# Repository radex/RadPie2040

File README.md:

# RadPie2040

A RP2040-based board, similar to [Raspberry Pi Pico H](https://www.raspberrypi.com/products/raspberry-pi-pico/), featuring:

- RP2040 microcontroller
- 16MB Flash
- breadboard-friendly pin headers with labels (+ debug header)
- USB-C connector
- BOOTSEL *and* RESET buttons
- **JLCPCB Assembly optimized**, 2-layer board
- KiCad 8 template, hierarchical schematic

**DISCLAIMER**: This board was designed as an exercise. It has not (yet) been manufactured and tested. Also, **I don't know what I'm doing**, this is like the third PCB I've designed. Don't use it lol.

|  |  |  |
| -- | -- | -- |

## Credits and learning resources

This project is a fork of [Sleepdealr/RP2040-designguide](https://github.com/Sleepdealr/RP2040-designguide). It bears little resemblance to the original, but it was a great starting point (and still contains some pieces of it).

I also took a lot of inspiration and knowledge from these YouTube videos:

- [MicroType Engineering - RP2040 KiCad 6 Hardware Design](https://www.youtube.com/watch?v=RNH-CL8GrF8)
- [Phil’s Lab - Raspberry Pi RP2040 Hardware Design](https://www.youtube.com/watch?v=X00Cm5LMNQk)

There's extra learning resources in the `Resources/` folder (copied from Sleepdealr's project).

## Components

This board is optimized to use JLCPCB Basic (or Extended Preferred) components as much as possible to make it cheap to manufacture at 2-5 pieces scale.

Some worth mentioning:

- Flash: C97521 - Winbond W25Q128JVSIQ - 128Mbit (16MB) NOR Flash
- Voltage Regulator: C5446 - XC6206
- Crystal: C9002 - 12MHz
- Buttons: C318884 - TS-1187A-B-A-B
- TVS diodes: C7420376 - SRV05-4

Most components are the same as in [Sleepdealr's design](https://github.com/Sleepdealr/RP2040-designguide). Differences: larger Flash, different TVS diodes, added buttons, power LED indicator, removed resettable fuse.

**Extended parts**: The only parts that are not on JLCPCB's Basic parts list (i.e. you'll pay $3 feeder fee per part) are the RP2040 and the USB-C connector. (Pin headers are not on the BOM, but you can add them).

## Customizability

Some things to consider:

- The 0Ω 1206 resistor is a placeholder for a resettable fuse. (There are none in JLC's Basic parts, but it's a good idea to have one)
- Flash storage and buttons could be replaced with smaller physical packages
- For size/cost/simplicity, you can remove buttons, USB, TVS, fuse placeholder, LED if you don't need them. You could even remove the crystal and rely on RP2040's ring oscillator if you don't need precise timing or max performance

## TODO

- Have this board manufactured, see if it works!
- I'm concerned about the crystal, it seems to me that layout and loading capacitors could be better, but they can be finnicky, and Sleepdealr's design works, so I didn't change anything.
- I'm thinking of designing a smaller version, optimized for use as a module with carrier boards (using 1mm pitch pin headers, not castellated holes like the original Pico for cost reasons)

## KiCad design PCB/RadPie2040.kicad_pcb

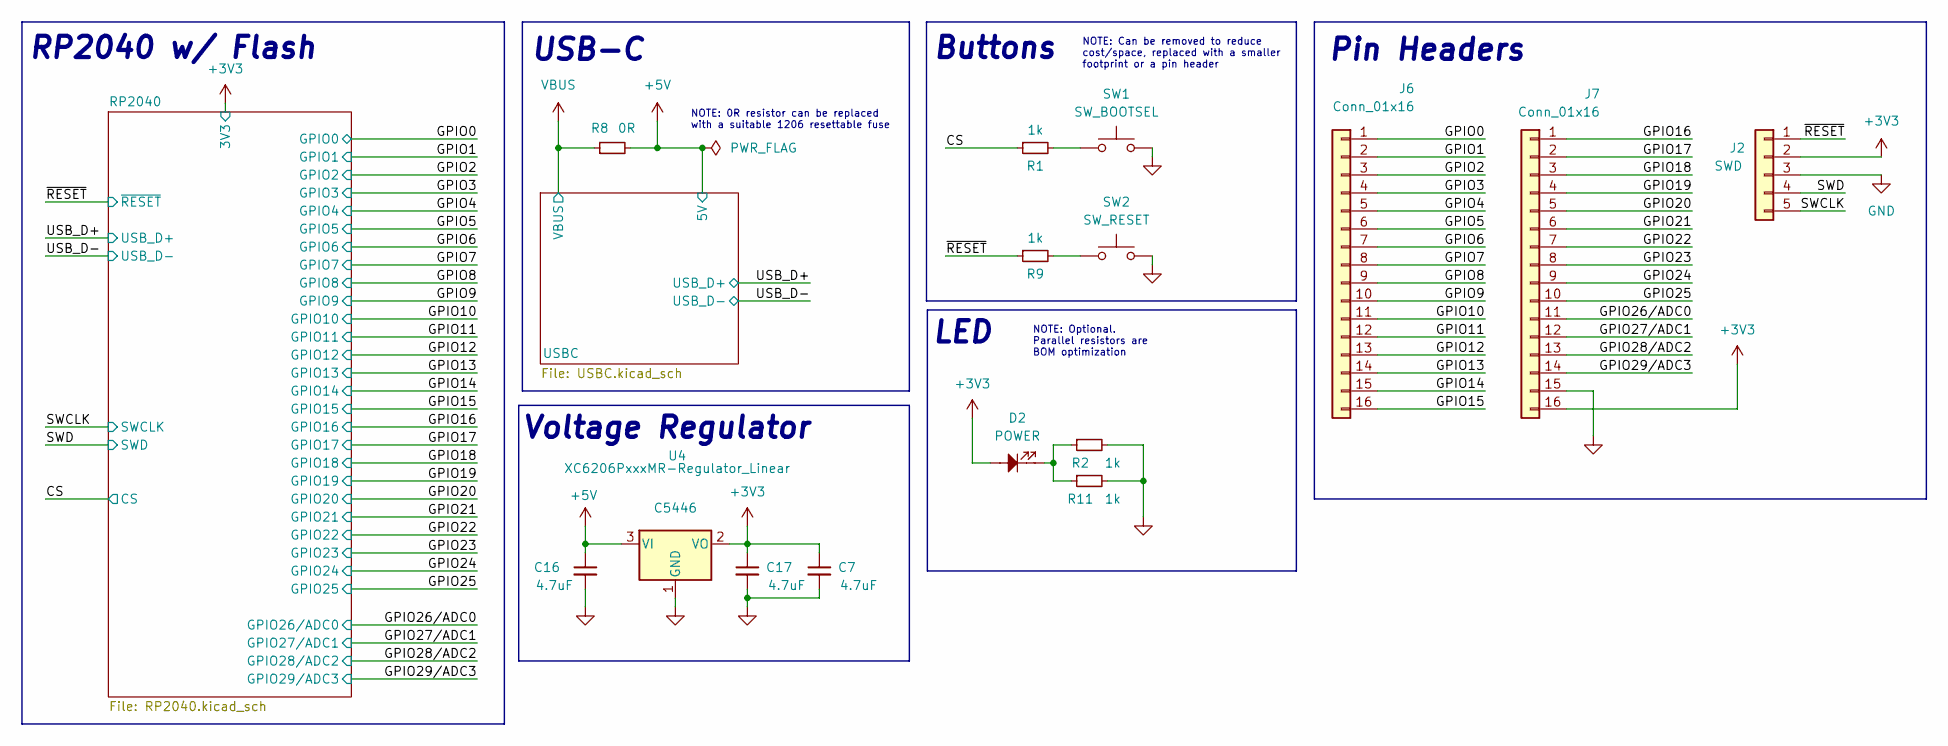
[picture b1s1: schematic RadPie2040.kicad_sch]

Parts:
C7, C16, C17: 4.7uF; C_0805_2012Metric; LCSC C1779
D2: POWER; LED_0603_1608Metric_Dot; LCSC C2286
J2: SWD; PinSocket_1x05_P2.54mm_Vertical
J6, J7: Conn_01x16; PinHeader_1x16_P2.54mm_Vertical
R1, R2, R9, R11: 1k; R_0402_1005Metric; LCSC C11702
R8: 0R; R_1206_3216Metric; LCSC C17888
SW1: SW_BOOTSEL; TS-1187A-B-A-B; LCSC C318884
SW2: SW_RESET; TS-1187A-B-A-B; LCSC C318884
U4: XC6206PxxxMR-Regulator_Linear; SOT-23; LCSC C5446

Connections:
+3V3: C7.1, C17.1, D2.2, J2.2, J7.16, U4.2 (VO); also elsewhere on the board
+5V: C16.1, R8.2, U4.3 (VI); also elsewhere on the board
/CS: R1.1; also elsewhere on the board
/GPIO0: J6.1; also elsewhere on the board
/GPIO1: J6.2; also elsewhere on the board
/GPIO2: J6.3; also elsewhere on the board
/GPIO3: J6.4; also elsewhere on the board
/GPIO4: J6.5; also elsewhere on the board
/GPIO5: J6.6; also elsewhere on the board
/GPIO6: J6.7; also elsewhere on the board
/GPIO7: J6.8; also elsewhere on the board
/GPIO8: J6.9; also elsewhere on the board
/GPIO9: J6.10; also elsewhere on the board
/GPIO10: J6.11; also elsewhere on the board
/GPIO11: J6.12; also elsewhere on the board
/GPIO12: J6.13; also elsewhere on the board
/GPIO13: J6.14; also elsewhere on the board
/GPIO14: J6.15; also elsewhere on the board
/GPIO15: J6.16; also elsewhere on the board
/GPIO16: J7.1; also elsewhere on the board
/GPIO17: J7.2; also elsewhere on the board
/GPIO18: J7.3; also elsewhere on the board
/GPIO19: J7.4; also elsewhere on the board
/GPIO20: J7.5; also elsewhere on the board
/GPIO21: J7.6; also elsewhere on the board
/GPIO22: J7.7; also elsewhere on the board
/GPIO23: J7.8; also elsewhere on the board
/GPIO24: J7.9; also elsewhere on the board
/GPIO25: J7.10; also elsewhere on the board
/GPIO26/ADC0: J7.11; also elsewhere on the board
/GPIO27/ADC1: J7.12; also elsewhere on the board
/GPIO28/ADC2: J7.13; also elsewhere on the board
/GPIO29/ADC3: J7.14; also elsewhere on the board
/SWCLK: J2.5; also elsewhere on the board
/SWD: J2.4; also elsewhere on the board
/~RESET: J2.1, R9.1; also elsewhere on the board
GND: C7.2, C16.2, C17.2, J2.3, J7.15, R2.2, R11.2, SW1.1, SW2.1, U4.1 (GND); also elsewhere on the board
unnamed: D2.1, R2.1, R11.1
unnamed: R1.2, SW1.2
unnamed: R9.2, SW2.2
VBUS: R8.1; also elsewhere on the board

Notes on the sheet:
NOTE: Optional. Parallel resistors are BOM optimization
NOTE: 0R resistor can be replaced with a suitable 1206 resettable fuse
NOTE: Can be removed to reduce cost/space, replaced with a smaller footprint or a pin header
RP2040 w/ Flash
Voltage Regulator
LED
USB-C
Buttons
Pin Headers

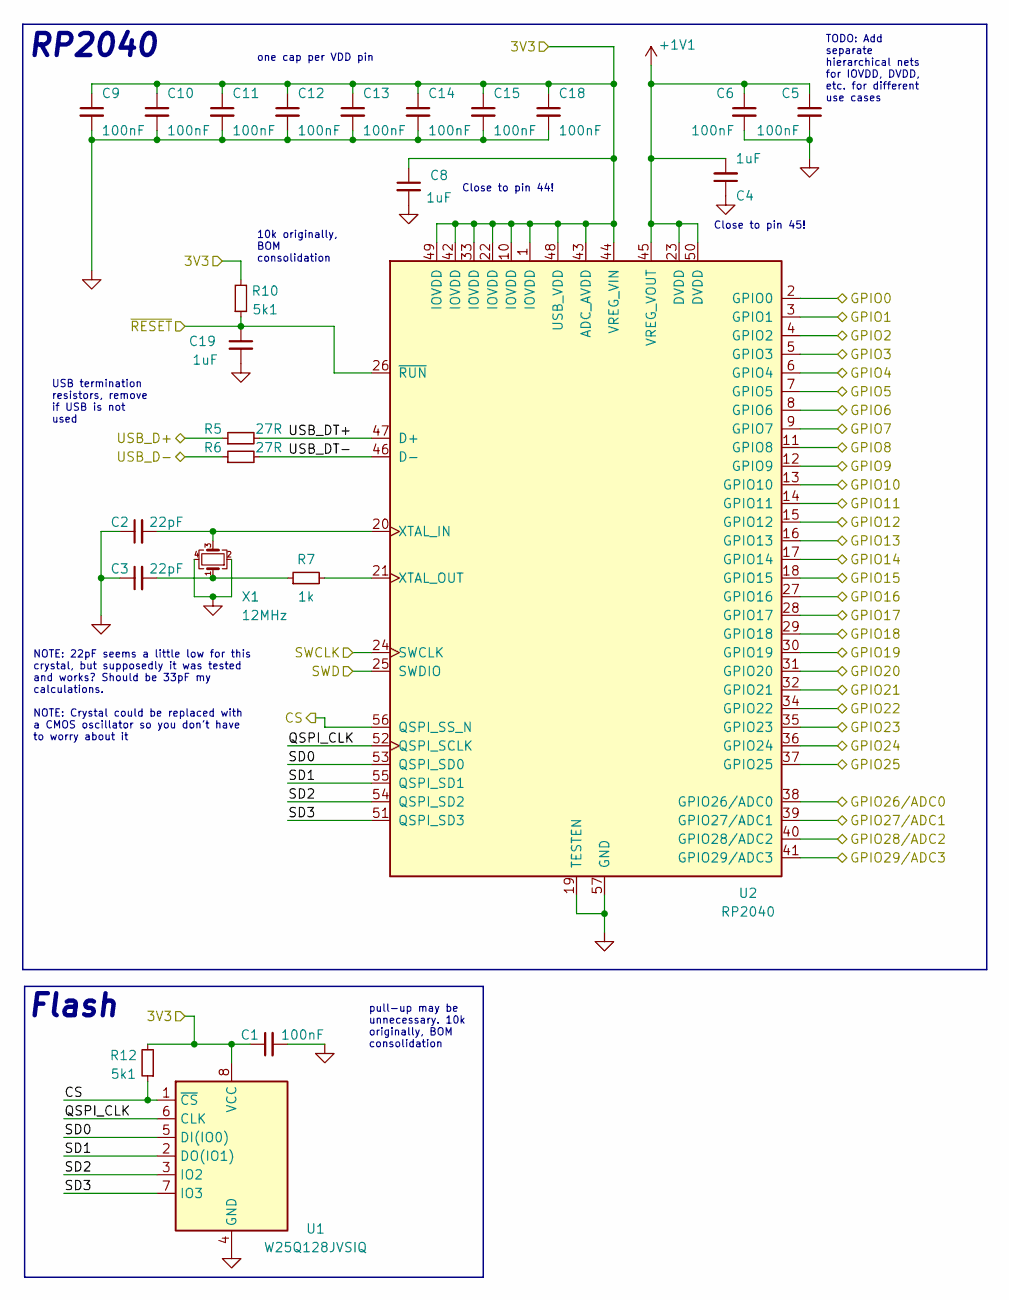
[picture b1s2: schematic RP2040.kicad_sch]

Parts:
C1, C5, C6, C9, C10, C11, C12, C13, C14, C15, C18: 100nF; C_0402_1005Metric; LCSC C1525
C2, C3: 22pF; C_0402_1005Metric; LCSC C1555
C4, C8, C19: 1uF; C_0402_1005Metric; LCSC C52923
R5, R6: 27R; R_0603_1608Metric; LCSC C25190
R7: 1k; R_0402_1005Metric; LCSC C11702
R10, R12: 5k1; R_0402_1005Metric; LCSC C25905
U1: W25Q128JVSIQ; SOIC-8_5.23x5.23mm_P1.27mm; LCSC C97521
U2: RP2040; RP2040-QFN-56; LCSC C2040
X1: 12MHz; Crystal_SMD_3225-4Pin_3.2x2.5mm; LCSC C9002

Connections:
+1V1: C4.2, C5.1, C6.1, U2.23 (DVDD), U2.45 (VREG_VOUT), U2.50 (DVDD)
+3V3: C1.1, C8.1, C9.1, C10.1, C11.1, C12.1, C13.1, C14.1, C15.1, C18.1, R10.2, R12.2, U1.8 (VCC), U2.1 (IOVDD), U2.10 (IOVDD), U2.22 (IOVDD), U2.33 (IOVDD), U2.42 (IOVDD), U2.43 (ADC_AVDD), U2.44 (VREG_VIN), U2.48 (USB_VDD), U2.49 (IOVDD); also elsewhere on the board
/CS: R12.1, U1.1 (~CS), U2.56 (QSPI_SS_N); also elsewhere on the board
/GPIO0: U2.2 (GPIO0); also elsewhere on the board
/GPIO1: U2.3 (GPIO1); also elsewhere on the board
/GPIO2: U2.4 (GPIO2); also elsewhere on the board
/GPIO3: U2.5 (GPIO3); also elsewhere on the board
/GPIO4: U2.6 (GPIO4); also elsewhere on the board
/GPIO5: U2.7 (GPIO5); also elsewhere on the board
/GPIO6: U2.8 (GPIO6); also elsewhere on the board
/GPIO7: U2.9 (GPIO7); also elsewhere on the board
/GPIO8: U2.11 (GPIO8); also elsewhere on the board
/GPIO9: U2.12 (GPIO9); also elsewhere on the board
/GPIO10: U2.13 (GPIO10); also elsewhere on the board
/GPIO11: U2.14 (GPIO11); also elsewhere on the board
/GPIO12: U2.15 (GPIO12); also elsewhere on the board
/GPIO13: U2.16 (GPIO13); also elsewhere on the board
/GPIO14: U2.17 (GPIO14); also elsewhere on the board
/GPIO15: U2.18 (GPIO15); also elsewhere on the board
/GPIO16: U2.27 (GPIO16); also elsewhere on the board
/GPIO17: U2.28 (GPIO17); also elsewhere on the board
/GPIO18: U2.29 (GPIO18); also elsewhere on the board
/GPIO19: U2.30 (GPIO19); also elsewhere on the board
/GPIO20: U2.31 (GPIO20); also elsewhere on the board
/GPIO21: U2.32 (GPIO21); also elsewhere on the board
/GPIO22: U2.34 (GPIO22); also elsewhere on the board
/GPIO23: U2.35 (GPIO23); also elsewhere on the board
/GPIO24: U2.36 (GPIO24); also elsewhere on the board
/GPIO25: U2.37 (GPIO25); also elsewhere on the board
/GPIO26/ADC0: U2.38 (GPIO26/ADC0); also elsewhere on the board
/GPIO27/ADC1: U2.39 (GPIO27/ADC1); also elsewhere on the board
/GPIO28/ADC2: U2.40 (GPIO28/ADC2); also elsewhere on the board
/GPIO29/ADC3: U2.41 (GPIO29/ADC3); also elsewhere on the board
/RP2040/QSPI_CLK: U1.6 (CLK), U2.52 (QSPI_SCLK)
/RP2040/SD0: U1.5 (DI(IO0)), U2.53 (QSPI_SD0)
/RP2040/SD1: U1.2 (DO(IO1)), U2.55 (QSPI_SD1)
/RP2040/SD2: U1.3 (IO2), U2.54 (QSPI_SD2)
/RP2040/SD3: U1.7 (IO3), U2.51 (QSPI_SD3)
/RP2040/USB_DT+: R5.2, U2.47 (D+)
/RP2040/USB_DT-: R6.2, U2.46 (D-)
/SWCLK: U2.24 (SWCLK); also elsewhere on the board
/SWD: U2.25 (SWDIO); also elsewhere on the board
/USB_D+: R5.1; also elsewhere on the board
/USB_D-: R6.1; also elsewhere on the board
/~RESET: C19.1, R10.1, U2.26 (~RUN); also elsewhere on the board
GND: C1.2, C2.1, C3.1, C4.1, C5.2, C6.2, C8.2, C9.2, C10.2, C11.2, C12.2, C13.2, C14.2, C15.2, C18.2, C19.2, U1.4 (GND), U2.19 (TESTEN), U2.57 (GND), X1.2, X1.4; also elsewhere on the board
unnamed: C3.2, R7.1, X1.1
unnamed: C2.2, U2.20 (XTAL_IN), X1.3
unnamed: R7.2, U2.21 (XTAL_OUT)

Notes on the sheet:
USB termination resistors, remove if USB is not used
Close to pin 45!
one cap per VDD pin
NOTE: 22pF seems a little low for this crystal, but supposedly it was tested and works? Should be 33pF my calculations. NOTE: Crystal could be replaced with a CMOS oscillator so you don't have to worry about it
10k originally, BOM consolidation
TODO: Add separate hierarchical nets for IOVDD, DVDD, etc. for different use cases
pull-up may be unnecessary. 10k originally, BOM consolidation
Close to pin 44!
RP2040
Flash

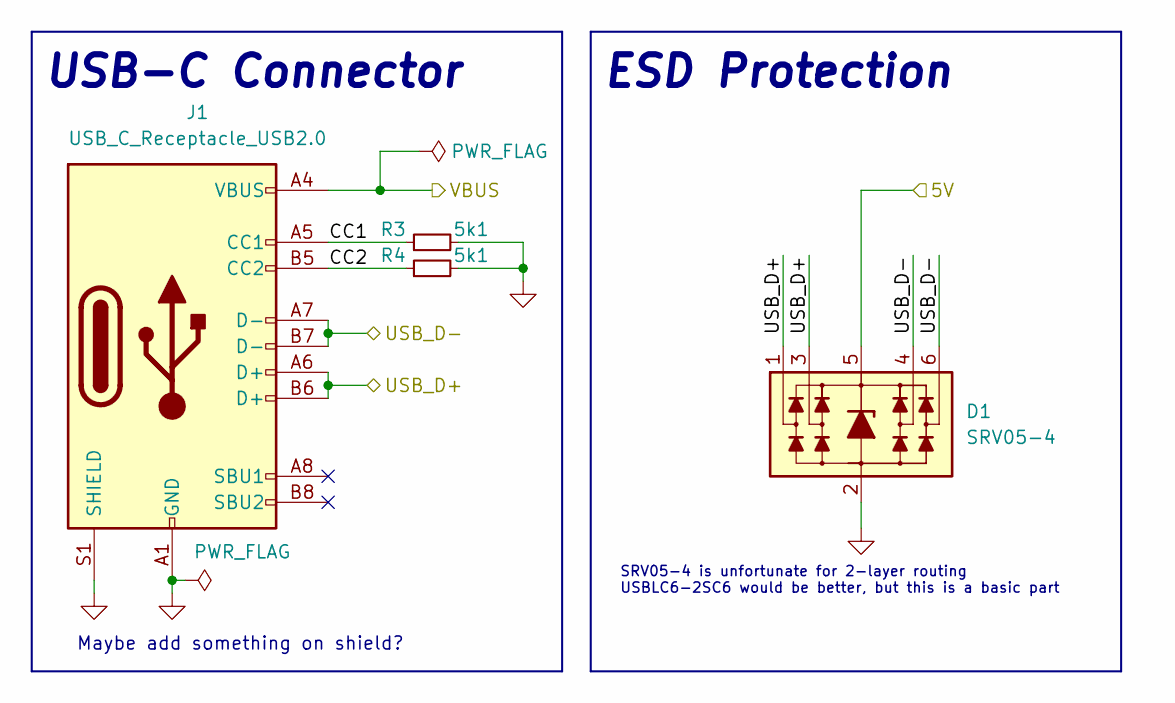
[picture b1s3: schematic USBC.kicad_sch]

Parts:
D1: SRV05-4; SOT-23-6; LCSC C7420376
J1: USB_C_Receptacle_USB2.0; USB_C_Receptacle_HRO_TYPE-C-31-M-12; LCSC C165948
R3, R4: 5k1; R_0402_1005Metric; LCSC C25905

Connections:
+5V: D1.5 (VP); also elsewhere on the board
/USBC/CC1: J1.A5 (CC1), R3.1
/USBC/CC2: J1.B5 (CC2), R4.1
/USB_D+: D1.1 (L1), D1.3 (L2), J1.A6 (D+), J1.B6 (D+); also elsewhere on the board
/USB_D-: D1.4 (L3), D1.6 (L4), J1.A7 (D-), J1.B7 (D-); also elsewhere on the board
GND: D1.2 (VN), J1.A1 (GND), J1.A12 (GND), J1.B1 (GND), J1.B12 (GND), J1.S1 (SHIELD), R3.2, R4.2; also elsewhere on the board
VBUS: J1.A4 (VBUS), J1.A9 (VBUS), J1.B4 (VBUS), J1.B9 (VBUS); also elsewhere on the board

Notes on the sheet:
USB-C Connector
SRV05-4 is unfortunate for 2-layer routing USBLC6-2SC6 would be better, but this is a basic part
ESD Protection
Maybe add something on shield?

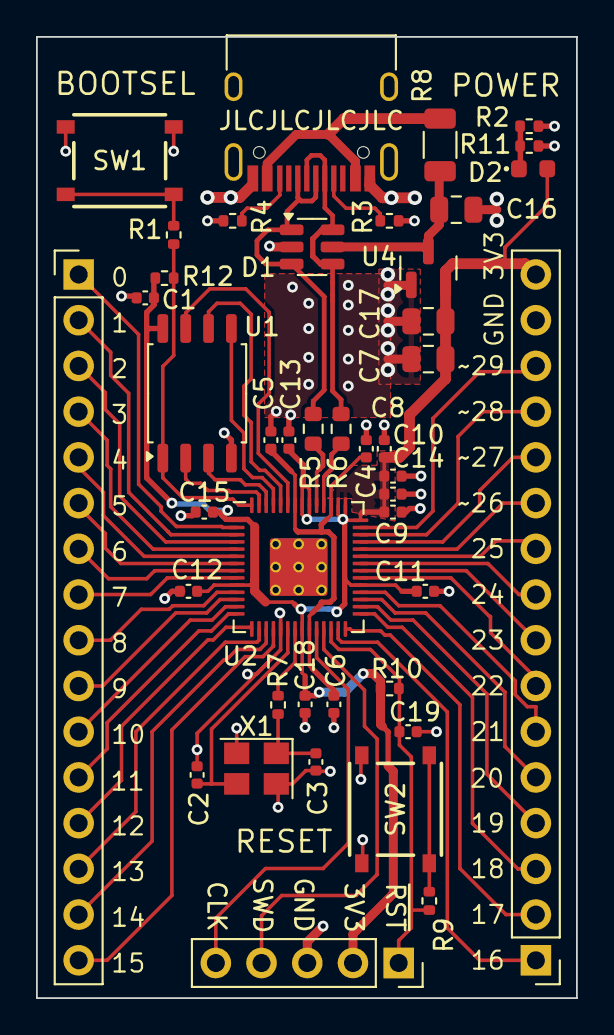
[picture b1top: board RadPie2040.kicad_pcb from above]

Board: 2 copper layers, 30.0 x 53.4 mm, 43 parts (0 on the bottom side), 56 nets.

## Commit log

2024-03-10 Add pull-up for Flash, just in case
2024-03-10 Refactor schematic to be hierarchical
2024-03-10 jlcpcb production fixes
